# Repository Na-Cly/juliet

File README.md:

# Juliet 
### A pro micro compatible Romeo
#### forked from https://github.com/coseyfannitutti/romeo

PCB Compatible with other romeo parts. Only PCB was customized. Other components still labeled Romeo where applicable.

Changes
- Updated schematic to use pro micro
- Updated traces
- Updated silkscreen

These changes will require a different firmware than the romeo firmware which has not been pushed to qmk.

matrix:
rows { F5, D2, D3, F4 }
cols { D1, D0, D4, C6, D7, E6, B4, B5, B1, B3, B2, B6}

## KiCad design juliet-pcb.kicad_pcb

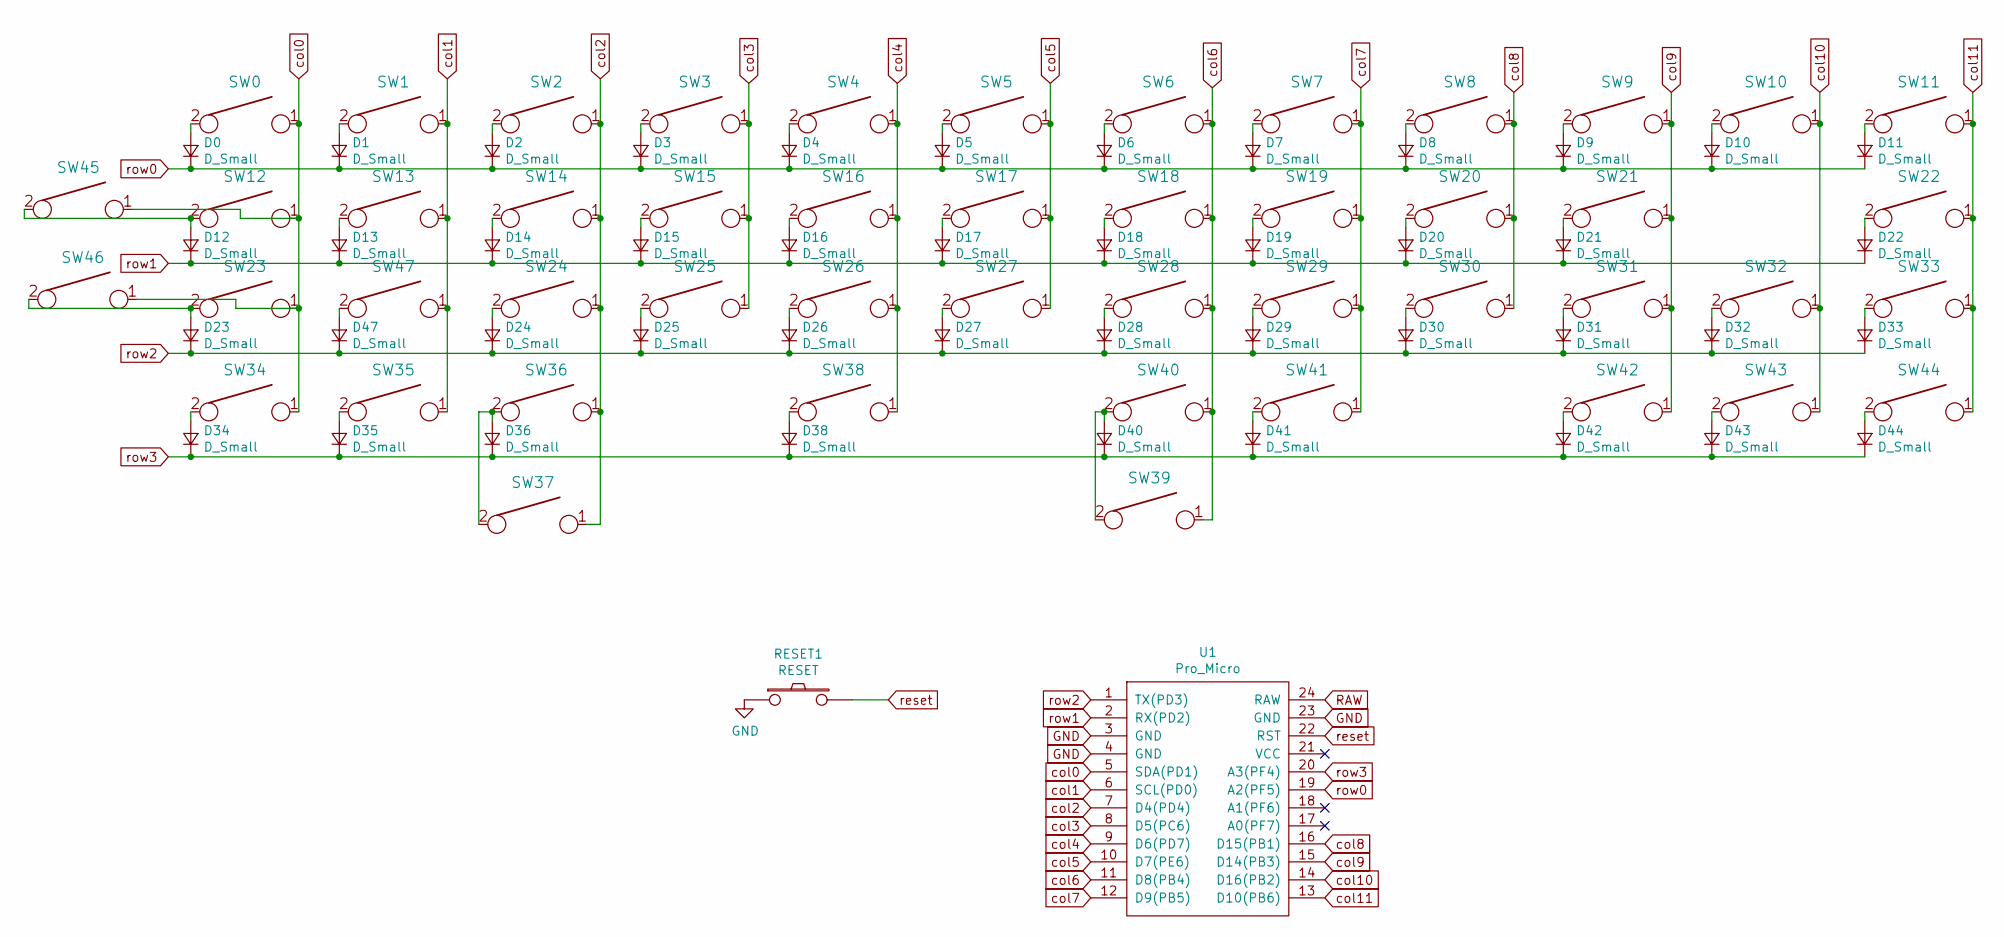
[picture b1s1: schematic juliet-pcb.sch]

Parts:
D0, D1, D2, D3, D4, D5, D6, D7, D8, D9, D10, D11, D12, D13, D14, D15, D16, D17, D18, D19, D20, D21, D22, D23, D24, D25, D26, D27, D28, D29, D30, D31, D32, D33, D34, D35, D36, D38, D40, D41, D42, D43, D44, D47: D_Small; D_DO-35_SOD27_P5.08mm_Horizontal
RESET1: RESET; SW_PUSH_6mm
SW0, SW11: KEYSW; SW_Cherry_MX1A_1.50u_PCBNOSCREEN
SW1, SW2, SW3, SW4, SW5, SW6, SW7, SW8, SW9, SW10, SW13, SW14, SW15, SW16, SW17, SW18, SW19, SW20, SW21, SW24, SW25, SW26, SW27, SW28, SW29, SW30, SW31, SW32, SW35, SW36, SW39, SW40, SW43, SW47: KEYSW; SW_Cherry_MX1A_1.00u_PCB-NOSCREEN
SW12, SW33: KEYSW; SW_Cherry_MX1A_1.75u_PCBNOSCREEN
SW22, SW23, SW38: KEYSW; SW_Cherry_MX1A_2.25u_PCBNOSCREEN
SW34, SW37, SW42, SW44, SW45, SW46: KEYSW; SW_Cherry_MX1A_1.25u_PCBNOSCREEN
SW41: KEYSW; SW_Cherry_MX1A_2.75u_PCB_NOSCREEN
U1: Pro_Micro; ArduinoProMicro-TopSide

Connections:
GND: RESET1.1, U1.3 (GND), U1.4 (GND), U1.23 (GND)
unnamed: D0.2 (A), SW0.2
unnamed: D1.2 (A), SW1.2
unnamed: D2.2 (A), SW2.2
unnamed: D3.2 (A), SW3.2
unnamed: D4.2 (A), SW4.2
unnamed: D5.2 (A), SW5.2
unnamed: D6.2 (A), SW6.2
unnamed: D7.2 (A), SW7.2
unnamed: D8.2 (A), SW8.2
unnamed: D9.2 (A), SW9.2
unnamed: D10.2 (A), SW10.2
unnamed: D11.2 (A), SW11.2
unnamed: D12.2 (A), SW12.2, SW45.2
unnamed: D13.2 (A), SW13.2
unnamed: D14.2 (A), SW14.2
unnamed: D15.2 (A), SW15.2
unnamed: D16.2 (A), SW16.2
unnamed: D17.2 (A), SW17.2
unnamed: D18.2 (A), SW18.2
unnamed: D19.2 (A), SW19.2
unnamed: D20.2 (A), SW20.2
unnamed: D21.2 (A), SW21.2
unnamed: D22.2 (A), SW22.2
unnamed: D23.2 (A), SW23.2, SW46.2
unnamed: D24.2 (A), SW24.2
unnamed: D25.2 (A), SW25.2
unnamed: D26.2 (A), SW26.2
unnamed: D27.2 (A), SW27.2
unnamed: D28.2 (A), SW28.2
unnamed: D29.2 (A), SW29.2
unnamed: D30.2 (A), SW30.2
unnamed: D31.2 (A), SW31.2
unnamed: D32.2 (A), SW32.2
unnamed: D33.2 (A), SW33.2
unnamed: D34.2 (A), SW34.2
unnamed: D35.2 (A), SW35.2
unnamed: D36.2 (A), SW36.2, SW37.2
unnamed: D38.2 (A), SW38.2
unnamed: D40.2 (A), SW39.2, SW40.2
unnamed: D41.2 (A), SW41.2
unnamed: D42.2 (A), SW42.2
unnamed: D43.2 (A), SW43.2
unnamed: D44.2 (A), SW44.2
unnamed: D47.2 (A), SW47.2
RAW: U1.24 (RAW)
col0: SW0.1, SW12.1, SW23.1, SW34.1, SW45.1, SW46.1, U1.5 (SDA(PD1))
col1: SW1.1, SW13.1, SW35.1, SW47.1, U1.6 (SCL(PD0))
col2: SW2.1, SW14.1, SW24.1, SW36.1, SW37.1, U1.7 (D4(PD4))
col3: SW3.1, SW15.1, SW25.1, U1.8 (D5(PC6))
col4: SW4.1, SW16.1, SW26.1, SW38.1, U1.9 (D6(PD7))
col5: SW5.1, SW17.1, SW27.1, U1.10 (D7(PE6))
col6: SW6.1, SW18.1, SW28.1, SW39.1, SW40.1, U1.11 (D8(PB4))
col7: SW7.1, SW19.1, SW29.1, SW41.1, U1.12 (D9(PB5))
col8: SW8.1, SW20.1, SW30.1, U1.16 (D15(PB1))
col9: SW9.1, SW21.1, SW31.1, SW42.1, U1.15 (D14(PB3))
col10: SW10.1, SW32.1, SW43.1, U1.14 (D16(PB2))
col11: SW11.1, SW22.1, SW33.1, SW44.1, U1.13 (D10(PB6))
reset: RESET1.2, U1.22 (RST)
row0: D0.1 (K), D1.1 (K), D2.1 (K), D3.1 (K), D4.1 (K), D5.1 (K), D6.1 (K), D7.1 (K), D8.1 (K), D9.1 (K), D10.1 (K), D11.1 (K), U1.19 (A2(PF5))
row1: D12.1 (K), D13.1 (K), D14.1 (K), D15.1 (K), D16.1 (K), D17.1 (K), D18.1 (K), D19.1 (K), D20.1 (K), D21.1 (K), D22.1 (K), U1.2 (RX(PD2))
row2: D23.1 (K), D24.1 (K), D25.1 (K), D26.1 (K), D27.1 (K), D28.1 (K), D29.1 (K), D30.1 (K), D31.1 (K), D32.1 (K), D33.1 (K), D47.1 (K), U1.1 (TX(PD3))
row3: D34.1 (K), D35.1 (K), D36.1 (K), D38.1 (K), D40.1 (K), D41.1 (K), D42.1 (K), D43.1 (K), D44.1 (K), U1.20 (A3(PF4))

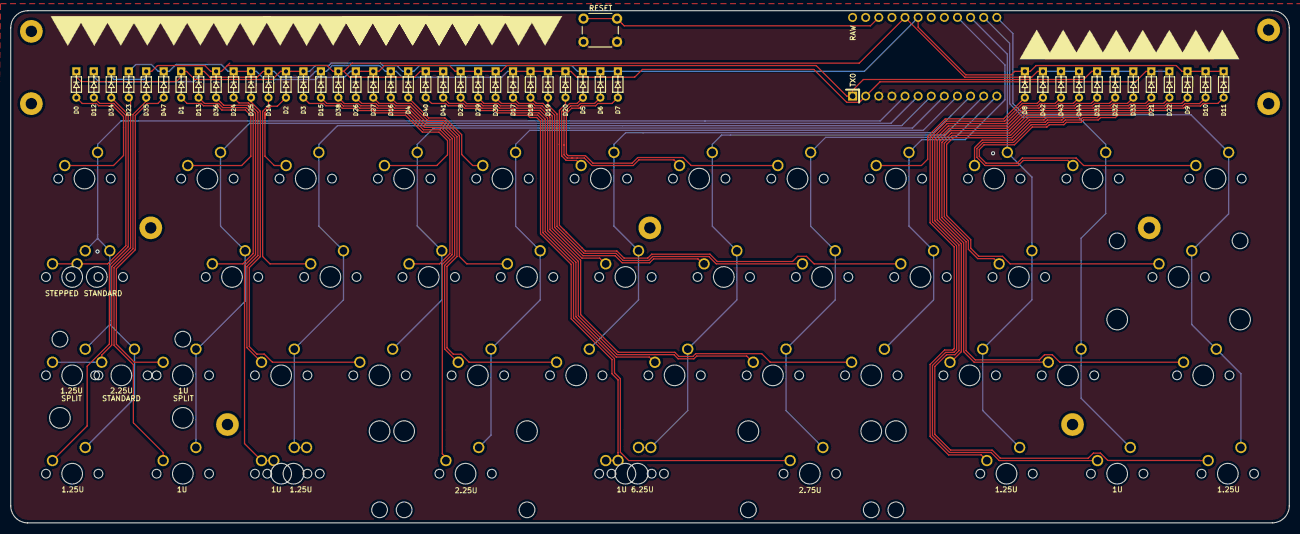
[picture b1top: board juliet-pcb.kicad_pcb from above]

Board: 2 copper layers, 247.6 x 99.2 mm, 95 parts (0 on the bottom side), 62 nets.

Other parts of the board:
ST39: 6.25U; MX-6.25U-Stabilizer

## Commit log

2020-04-30 rev1
2020-04-30 Final
2020-04-30 lol fixed
2020-04-30 Fixed the issues.
2020-05-01 gerber files
2020-05-01 Updated pro micro location
2020-05-01 Fixed a lot of issues.

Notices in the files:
juliet-pcb.kicad_pcb:
GPLv3
